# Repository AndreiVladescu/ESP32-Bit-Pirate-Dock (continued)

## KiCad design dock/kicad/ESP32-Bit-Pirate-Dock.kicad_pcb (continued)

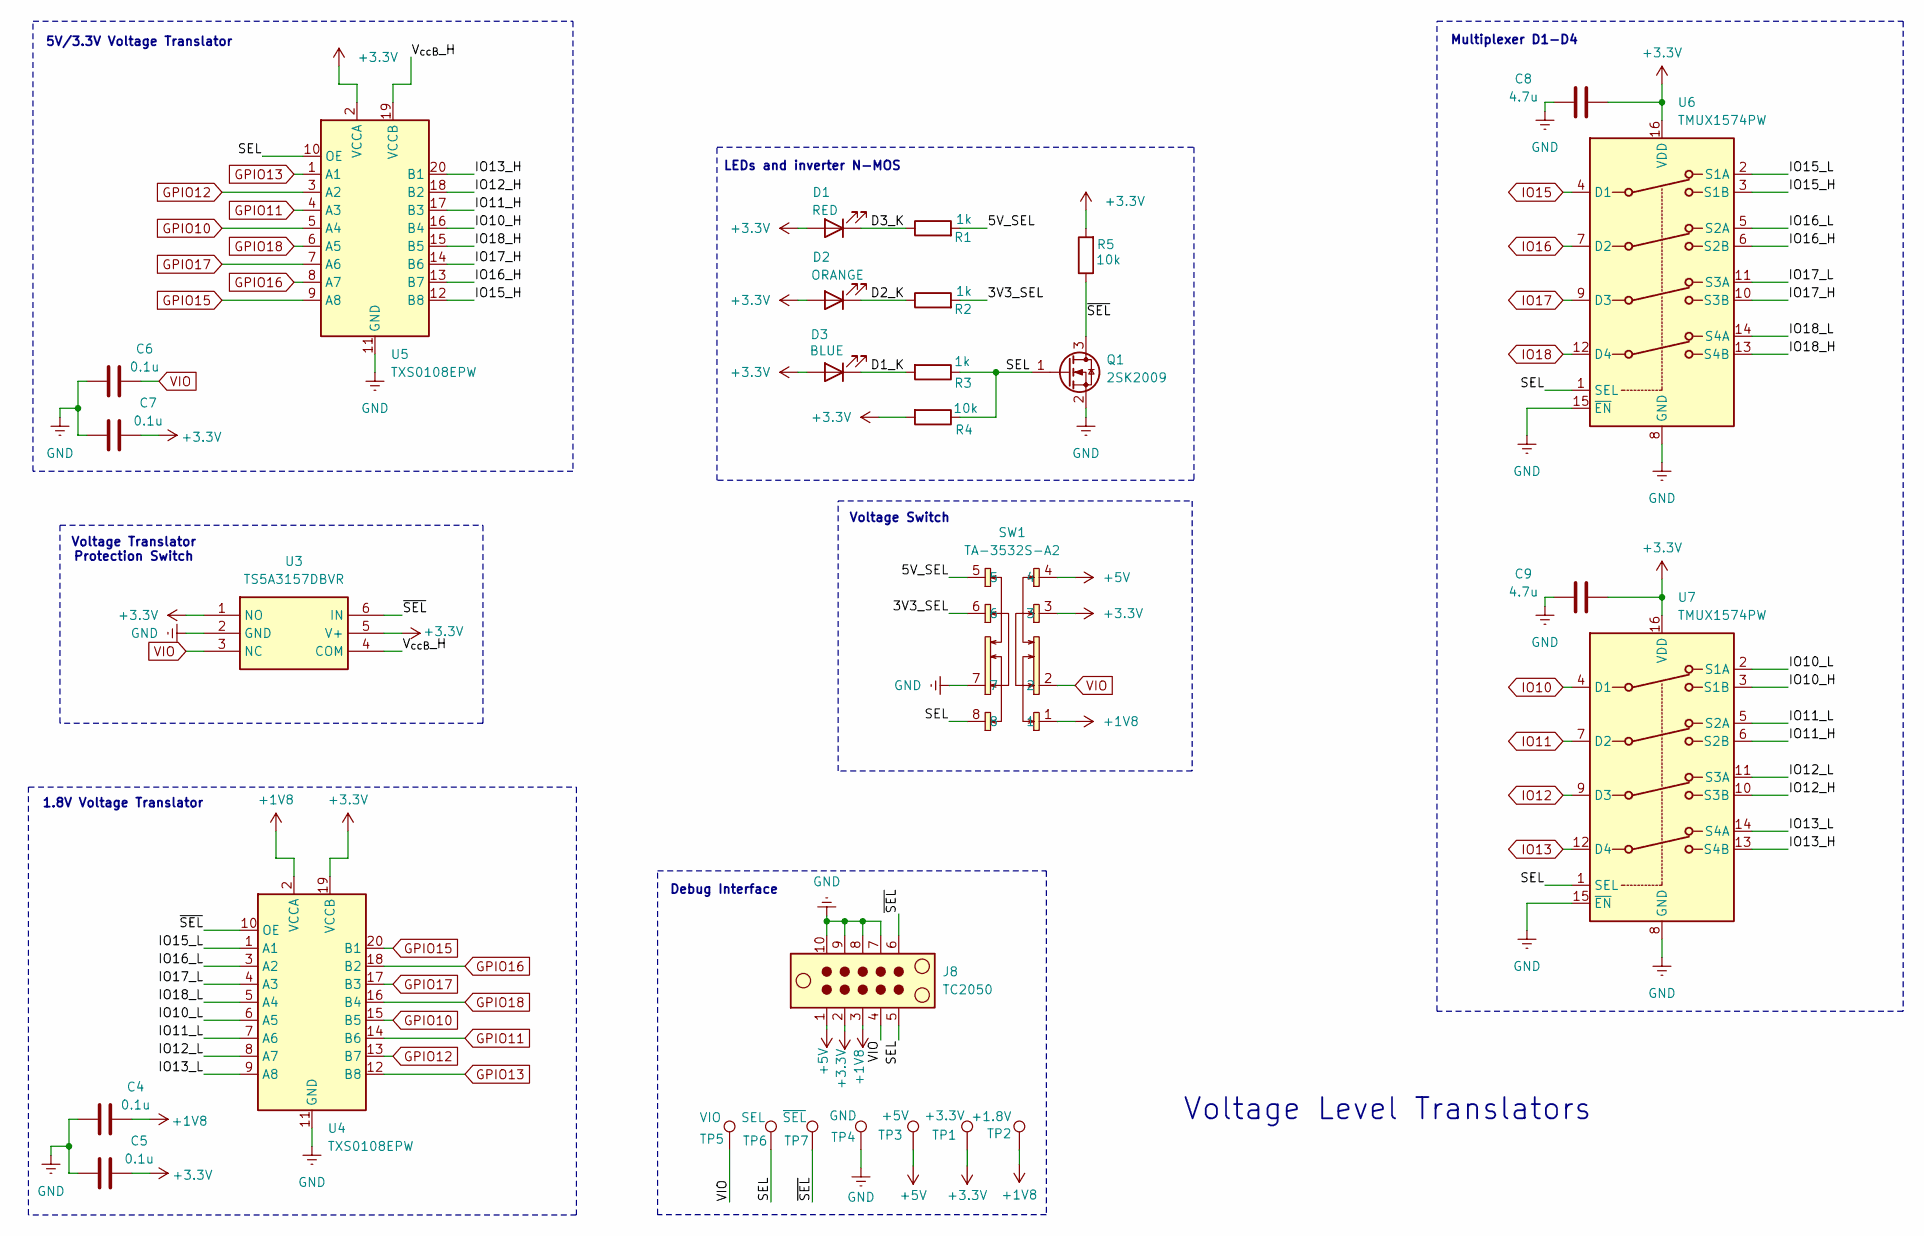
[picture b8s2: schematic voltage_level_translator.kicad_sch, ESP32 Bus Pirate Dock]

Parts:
C4, C5, C6, C7: 0.1u; C_0805_2012Metric
C8, C9: 4.7u; C_0805_2012Metric
D1: RED; LED_0805_2012Metric
D2: ORANGE; LED_0805_2012Metric
D3: BLUE; LED_0805_2012Metric
J8: TC2050; Tag-Connect_TC2050-IDC-NL_2x05_P1.27mm_Vertical_with_bottom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
Q1: 2SK2009; SOT-23
R1, R2, R3: 1k; R_0805_2012Metric
R4, R5: 10k; R_0805_2012Metric
SW1: TA-3532S-A2; SW-SMD_8P-L13.0-W3.5-P2.00; LCSC Part C514040
TP1: +3.3V; TestPoint_Pad_D1.0mm
TP2: +1.8V; TestPoint_Pad_D1.0mm
TP3: +5V; TestPoint_Pad_D1.0mm
TP4: GND; TestPoint_Pad_D1.0mm
TP5: VIO; TestPoint_Pad_D1.0mm
TP6: SEL; TestPoint_Pad_D1.0mm
TP7: ~{SEL}; TestPoint_Pad_D1.0mm
U3: TS5A3157DBVR; SOT95P280X145-6N; Mouser Part Number 595-TS5A3157DBVR
U4, U5: TXS0108EPW; Texas_PW0020A_TSSOP-20_4.4x6.5mm_P0.65mm
U6, U7: TMUX1574PW; TSSOP-16_4.4x5mm_P0.65mm

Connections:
+1V8: C4.1, J8.3, SW1.1, TP2.1, U4.2 (VCCA); also elsewhere on the board
+3.3V: C5.1, C7.1, C8.1, C9.1, D1.2 (A), D2.2 (A), D3.2 (A), J8.2, R4.2, R5.2, SW1.3, TP1.1, U3.1 (NO), U3.5 (V+), U4.19 (VCCB), U5.2 (VCCA), U6.16 (VDD), U7.16 (VDD); also elsewhere on the board
+5V: J8.1, SW1.4, TP3.1; also elsewhere on the board
/Voltage Level Translator/3V3_SEL: R2.2, SW1.6
/Voltage Level Translator/5V_SEL: R1.2, SW1.5
/Voltage Level Translator/D1_K: D3.1 (K), R3.2
/Voltage Level Translator/D2_K: D2.1 (K), R2.1
/Voltage Level Translator/D3_K: D1.1 (K), R1.1
/Voltage Level Translator/IO10_H: U5.16 (B4), U7.3 (S1B)
/Voltage Level Translator/IO10_L: U4.6 (A5), U7.2 (S1A)
/Voltage Level Translator/IO11_H: U5.17 (B3), U7.6 (S2B)
/Voltage Level Translator/IO11_L: U4.7 (A6), U7.5 (S2A)
/Voltage Level Translator/IO12_H: U5.18 (B2), U7.10 (S3B)
/Voltage Level Translator/IO12_L: U4.8 (A7), U7.11 (S3A)
/Voltage Level Translator/IO13_H: U5.20 (B1), U7.13 (S4B)
/Voltage Level Translator/IO13_L: U4.9 (A8), U7.14 (S4A)
/Voltage Level Translator/IO15_H: U5.12 (B8), U6.3 (S1B)
/Voltage Level Translator/IO15_L: U4.1 (A1), U6.2 (S1A)
/Voltage Level Translator/IO16_H: U5.13 (B7), U6.6 (S2B)
/Voltage Level Translator/IO16_L: U4.3 (A2), U6.5 (S2A)
/Voltage Level Translator/IO17_H: U5.14 (B6), U6.10 (S3B)
/Voltage Level Translator/IO17_L: U4.4 (A3), U6.11 (S3A)
/Voltage Level Translator/IO18_H: U5.15 (B5), U6.13 (S4B)
/Voltage Level Translator/IO18_L: U4.5 (A4), U6.14 (S4A)
/Voltage Level Translator/SEL: J8.5, Q1.1 (G), R3.1, R4.1, SW1.8, TP6.1, U5.10 (OE), U6.1 (SEL), U7.1 (SEL)
/Voltage Level Translator/V_{ccB}_H: U3.4 (COM), U5.19 (VCCB)
/Voltage Level Translator/~SEL: J8.6, Q1.3 (D), R5.1, TP7.1, U3.6 (IN), U4.10 (OE)
GND: C4.2, C5.2, C6.2, C7.2, C8.2, C9.2, J8.7, J8.8, J8.9, J8.10, Q1.2 (S), SW1.7, TP4.1, U3.2 (GND), U4.11 (GND), U5.11 (GND), U6.8 (GND), U6.15 (~EN), U7.8 (GND), U7.15 (~EN); also elsewhere on the board
GPIO10: U4.15 (B5), U5.5 (A4); also elsewhere on the board
GPIO11: U4.14 (B6), U5.4 (A3); also elsewhere on the board
GPIO12: U4.13 (B7), U5.3 (A2); also elsewhere on the board
GPIO13: U4.12 (B8), U5.1 (A1); also elsewhere on the board
GPIO15: U4.20 (B1), U5.9 (A8); also elsewhere on the board
GPIO16: U4.18 (B2), U5.8 (A7); also elsewhere on the board
GPIO17: U4.17 (B3), U5.7 (A6); also elsewhere on the board
GPIO18: U4.16 (B4), U5.6 (A5); also elsewhere on the board
IO10: U7.4 (D1); also elsewhere on the board
IO11: U7.7 (D2); also elsewhere on the board
IO12: U7.9 (D3); also elsewhere on the board
IO13: U7.12 (D4); also elsewhere on the board
IO15: U6.4 (D1); also elsewhere on the board
IO16: U6.7 (D2); also elsewhere on the board
IO17: U6.9 (D3); also elsewhere on the board
IO18: U6.12 (D4); also elsewhere on the board
VIO: C6.1, J8.4, SW1.2, TP5.1, U3.3 (NC); also elsewhere on the board

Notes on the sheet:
Voltage Level Translators
5V/3.3V Voltage Translator
Voltage Switch
LEDs and inverter N-MOS
Debug Interface
Voltage Translator Protection Switch
Multiplexer D1-D4
1.8V Voltage Translator

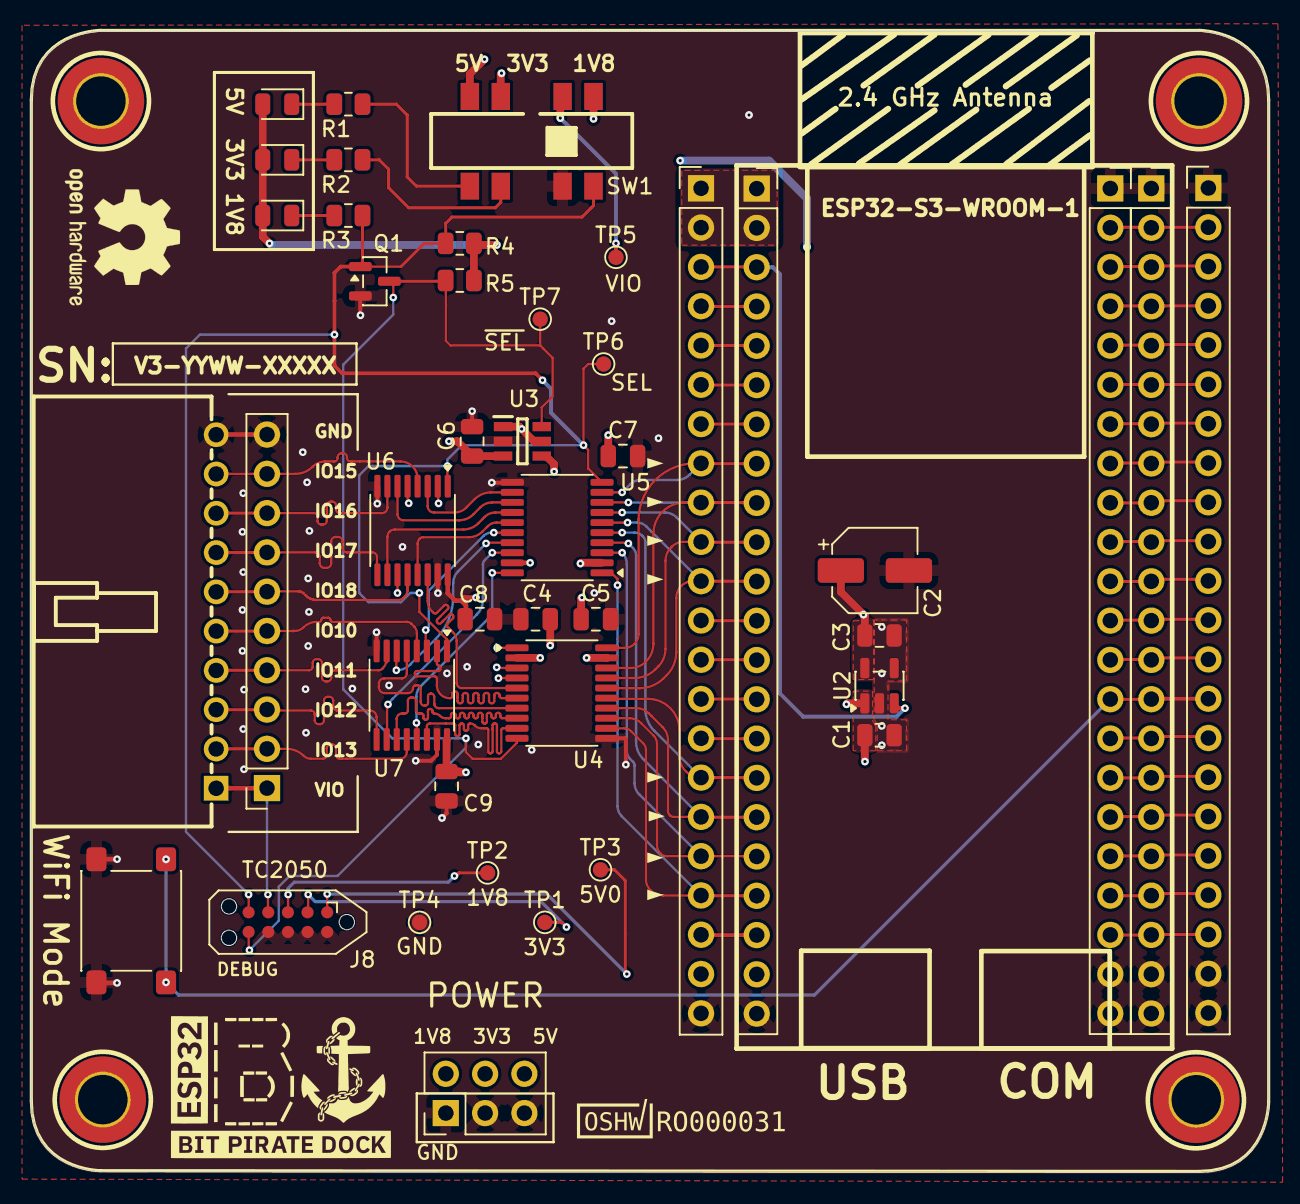
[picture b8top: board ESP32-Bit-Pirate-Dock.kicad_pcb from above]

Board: 4 copper layers, 80.0 x 73.8 mm, 46 parts (0 on the bottom side), 74 nets.

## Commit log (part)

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2026-05-08 Changed logo
2026-05-08 Added new name for kicad project
2026-05-17 Updated C5 schematic
2026-05-17 Added SPDT switch
2026-05-17 Initial PCB placement
2026-05-18 Updated c5 adapter PCB placement
2026-05-18 Updated silkscreen on C5 adapter
2026-05-18 Silkscreen minor additions
2026-05-27 Added latest dock model
2026-05-27 Updated 3D models & photos
2026-06-05 Updated pcb image
2026-06-05 Rename 'Bus' to 'Bit'
2026-06-16 Modified silkscreen markings
2026-06-16 Inverted port writing
2026-06-29 Updated photos
